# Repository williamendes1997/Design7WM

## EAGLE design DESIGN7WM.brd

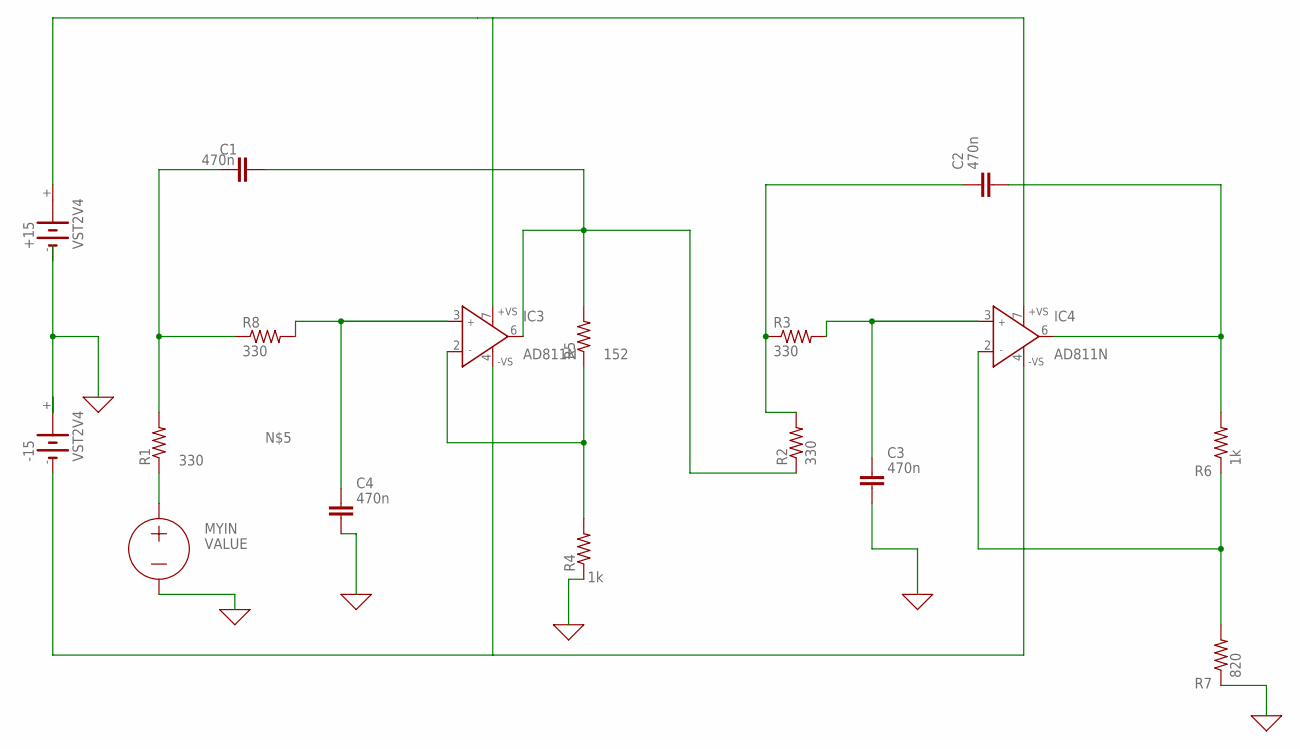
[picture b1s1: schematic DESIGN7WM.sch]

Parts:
+15: VST2V4; VST2
-15: VST2V4; VST2
IC3, IC4: AD811N; DIL08
R1, R2, R3, R8: 330; VTA52
R4, R6: 1k; VTA52
R5: 152; VTA52
R7: 820; VTA52

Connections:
0: +15.-, -15.+, -15.+@1 (+), R4.1, R7.1
unnamed: IC3.3 (IN+), R8.2
unnamed: -15.-, IC3.4 (-VS), IC4.4 (-VS)
unnamed: +15.+, IC3.7 (+VS), IC4.7 (+VS)
unnamed: R1.2, R8.1
unnamed: IC4.3 (IN+), R3.2
unnamed: IC4.2 (IN-), R6.1, R7.2
unnamed: IC3.2 (IN-), R4.2, R5.1
unnamed: IC3.6 (OUT), R2.1, R5.2
unnamed: IC4.6 (OUT), R6.2
unnamed: R2.2, R3.1

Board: 2 copper layers, 12 parts (0 on the bottom side), 11 nets, no tracks yet.
